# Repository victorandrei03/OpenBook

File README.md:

# OpenBook - 331CC Preda Victor-Andrei

## 📋 Descriere Proiect
Acest proiect reprezintă o placă electronică (e-board) customizată, proiectată în Autodesk Fusion 360. Include:
- Schematică completă
- Design PCB
- Design 3D al carcasei
- Listă completă de componente (BOM)

## 🗂️ Diagrama bloc

## 🛠️ Componente Cheie
| Componentă | Model | Descriere |
|------------|-------|-----------|
| **Microcontroler** | ESP32-C6-WROOM-1-N8 | MCU principal cu WiFi/Bluetooth LE |
| **Ceas RTC** | DS3231SN# | Ceas în timp real cu compensare de temperatură |
| **Senzori** | BME680 | Senzor ambiental (temperatură, umiditate, presiune, VOC) |
| **Management Power** | BD5229G-TR + MCP73831 | Sistem complet de încărcare baterii |

## 📊 Bill of Materials (BOM)

### 🔌 Conectori & Interfețe
| Part Name | Device | Link |
|-----------|--------|------|
| J1 | FH34SRJ-24S-0.5SH_99_ | [Datasheet](https://componentsearchengine.com/part-view/XC6220A331MR-G/Torex) |
| J2 | USB4110-GF-A | [Mouser](https://componentsearchengine.com/part-view/USB4110-GF-A/GCT) |
| J3 | QWIIC_CONNECTORJS-1MM | [SparkFun](https://www.sparkfun.com/products/14417) |

### 💾 Memorie & Storage
| Part Name | Device | Link |
|-----------|--------|------|
| U1 | W25Q512JVEIQ | [Winbond](https://www.snapeda.com/parts/W25Q512JVEIQ/Winbond+Electronics/view-part/) |

### ⚡ Power Management
| Part Name | Device | Link |
|-----------|--------|------|
| IC1 | BD5229G-TR | [ROHM](https://componentsearchengine.com/part-view/BD5229G-TR/ROHM) |
| U4 | MAX17048G+T10 | [Analog Devices](https://www.snapeda.com/parts/MAX17048G+T10/Analog+Devices/view-part/) |

### 🎚️ Componente Pasive
| Categorie | Qty | Device | Link |
|-----------|-----|--------|------|
| **Rezistoare** | 25+ | RR0402 100K | [YAGEO](https://componentsearchengine.com/part-view/R0402%201%25%20100%20K/YAGEO) |
| **Condensatoare** | 20+ | CC0402 1µF | [YAGEO](https://componentsearchengine.com/part-view/CC0402MRX5R5BB106/YAGEO) |
| **Inductoare** | 1 | 744043680 | [Würth](https://eu.mouser.com/ProductDetail/Wurth-Elektronik/744043680) |

### 🛑 Protecții & Diodes
| Part Name | Device | Link |
|-----------|--------|------|
| D1 | USBLC6-2SC6Y | [STMicro](https://www.snapeda.com/parts/USBLC6-2SC6Y/STMicroelectronics/view-part/) |
| D3-D5 | MBR0530 | [Mouser](https://eu.mouser.com/ProductDetail/KYOCERA-AVX/SD0805S020S1R0) |

## 🛠️ Descriere Hardware Detaliată

### 1. Microcontroller - ESP32-C6-WROOM-1-N8
**Specificații Avansate:**
- **Arhitectură:** RISC-V single-core cu 160MHz (configurabil dinamic)
- **Memorie:**
  - 320KB SRAM intern (pentru date)
  - 512KB ROM (pentru bootloader)
  - 8MB Flash SPI (W25Q512JVEIQ) - stochează firmware și date utilizator
- **Conectivitate:**
  - **WiFi 6** (802.11ax) cu throughput de până la 300Mbps
  - **Bluetooth 5 LE** cu support Mesh
  - **Zigbee 3.0** pentru IoT industrial
- **Periferice Integrate:**
  - 4× controller SPI (inclusiv Quad-SPI)
  - 2× I²C (software configurable)
  - 2× UART (cu flow control hardware)
  - 1× USB 2.0 OTG Full-Speed

**Management Energie:**
- **Moduri de operare:**
  - Active Mode: 80mA @ 160MHz
  - Light Sleep: 1.5mA (perif. RAM păstrate)
  - Deep Sleep: 20µA (doar RTC activ)
- **Feature-uri speciale:**
  - Wake-up din Deep Sleep prin:
    - GPIO
    - Timer RTC
    - UART
    - Senzor BME680 (via interrupt)
   
---

### 2. Sistem de Alimentare

**Componente Cheie:**
1. **MCP73831**
   - Curent de încărcare programabil: 100-500mA
   - Protecții integrate: Over-voltage, Reverse discharge
   - LED indicator de stare (conectat la GPIO18)

2. **BD5229G-TR**
   - Eficiență 92% @ 500mA load
   - Ripple voltage < 50mV
   - Shutdown current < 1µA

3. **MAX17048G+T10**
   - Precizie măsurare: ±1% SOC
   - Alertă baterie critică (conectat la GPIO15)
   - Consum propriu: 7µA în mod normal

---

### 3. Senzori & Periferice

#### 3.1 Senzor Environmental BME680
**Interfață:** I²C @ 400kHz (adresă 0x76)  
**Caracteristici unice:**
- **Algoritm BSEC** pentru calcul IAQ (Indice Calitate Aer)
- **Compensare automată** a variațiilor de temperatură
- **Calibrare în fabrică** pentru precizie ridicată

**Conexiuni:**
| Pin BME680 | Pin ESP32 | Notă |
|------------|-----------|------|
| VDD        | 3.3V      | Alimentare filtrată |
| GND        | GND       | - |
| SDA        | GPIO1     | Cu pull-up 4.7kΩ |
| SCL        | GPIO2     | Cu pull-up 4.7kΩ |

#### 3.2 Real-Time Clock DS3231SN#
**Precizie:** ±2ppm (echiv. ~1min/an)  
**Backup:** Supercondensator CPH3225A (10F @ 3.3V)  
**Funcționalități:**
- Alarmă programabilă
- Output square wave (1Hz-32kHz)
- Temperatură internă compensată

---

### 4. Interfețe Externe

#### 4.1 Port USB-C
**Implementare:**
- **Controler:** USB PHY integrat în ESP32-C6
- **Protecții:**
  - ESD: USBLC6-2SC6Y (8kV IEC61000-4-2)
  - Current limit: Polyfuse 500mA

**Funcționalități:**
1. Încărcare baterie
2. Serial Console (CDC-ACM)
3. Update firmware (DFU mode)

#### 4.2 Conector Qwiic
**Aplicații:**
- Conectare senzori adiționali
- Debug I²C bus
- Extensii custom

---

## 🔌 Mapare Pini ESP32-C6

| Pin ESP32-C6 | Componentă / Semnal | Motivul Alegerii |
|--------------|----------------------|------------------|
| **GPIO1 (SDA)** | Magistrală I²C (BME680, MAX17048, DS3231) | Permite comunicarea simultană cu multiple dispozitive prin protocol standard |
| **GPIO2 (SCL)** | Semnal de sincronizare I²C | Asigură temporizarea corectă a transferurilor pe magistrala shared I²C |
| **GPIO5** | SPI MISO (E-Paper) | Facilitatează recepția datelor de stare de la display |
| **GPIO6** | SPI MOSI (E-Paper) | Canal dedicat pentru transmiterea imaginilor către ecran |
| **GPIO7** | SPI CLK (E-Paper) | Generează semnalul de ceas pentru sincronizarea datelor SPI |
| **GPIO8** | SPI CS (E-Paper) | Selectează exclusiv display-ul în configurații multi-slave |
| **GPIO9** | E-Paper DC | Determină dacă transferul conține date sau comenzi |
| **GPIO10** | E-Paper RST | Permite resetarea hardware a display-ului în caz de eroare |
| **GPIO11** | E-Paper BUSY | Monitorizează starea de ocupat pentru sincronizare fără polling |
| **GPIO12** | BUTTON_BOOT | Configurat special pentru intrare în modul de programare |
| **GPIO13** | BUTTON_RESET | Asigură resetarea controlată a sistemului |
| **GPIO14** | BUTTON_USER | Permite interacțiunea utilizatorului cu meniul principal |
| **GPIO15** | MAX17048 ALERT | Semnalează stări critice ale bateriei prin interrupt |
| **GPIO16** | USB D+ | Implementare directă a fizicului USB conform specificației |
| **GPIO17** | USB D- | Pereche diferențială obligatorie pentru comunicarea USB |
| **GPIO18** | STATUS_LED | Oferă feedback vizual despre starea sistemului |
| **GPIO19** | SD Card CS | Selectează cardul SD în arhitectura SPI shared |
| **GPIO20** | SD Card MISO | Primește date de la memoria externă |
| **GPIO21** | SD Card MOSI | Transmite comenzi și date către cardul SD |
| **GPIO4** | SD Card CLK | Asigură sincronizarea transferurilor SPI către/storage |

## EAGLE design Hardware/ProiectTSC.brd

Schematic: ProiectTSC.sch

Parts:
BOOT_BUTTON1: BUTTON_CUSYOMV1; MYBUTTON
C1, C2, C4_USB, C6, C8, C9, C10: 100nF; EAGLE-LTSPICE_C0402
C1_BAT, C1_BAT1, C1_BAT2: 4.7uF; ESP32_WROVER_EAGLE-LTSPICE_C0402
C2_BAT, C5_USB: 4.7uF; EAGLE-LTSPICE_C0402
C3: 100uF; RCL_CT3528
C4: 4.7uF/25V; ESP32_WROVER_EAGLE-LTSPICE_C0402
C5: 1uF; EAGLE-LTSPICE_C0402
C7: 10uF; ESP32_WROVER_EAGLE-LTSPICE_C0402
C10_SUPERCAP: CPH3225A; CAPCP3225X100N
CHANGE_BUTTON: BUTTON_CUSYOMV1; MYBUTTON
CHG_LED: ADAFRUIT_LEDCHIP-LED0603; ADAFRUIT_CHIP-LED0603
C_DELAY: 100nF; EAGLE-LTSPICE_C0402
D1: USBLC6-2SC6Y; SOT95P280X145-6N
D2, D7: ESP32_WROVER_AVX---SD0805S020S1R0_AVX_SD0805S020S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; ESP32_WROVER_AVX---SD0805S020S1R0_AVX_SD0805S020S1R0_0
D3, D4, D5: MBR0530; SOD3716X135N
D6, D8, D9, D10, D11, D12: PGB1010603MR; DIOC1608X36N
EPD_C1, EPD_C2, EPD_C6, EPD_C7, EPD_C8, EPD_C9, EPD_C10, EPD_C11, EPD_C12: 1uF/50V; EAGLE-LTSPICE_C0402
EPD_C5: 0.1uF/50V; EAGLE-LTSPICE_C0402
IC1: BD5229G-TR; SOT95P280X125-5N
IC4: XC6220A331MR-G; SOT95P280X120-5N
J1: FH34SRJ-24S-0.5SH_99_; FH34SRJ24S05SH99
J2: SAMACSYS_PARTS_USB4110-GF-A; SAMACSYS_PARTS_USB4110GFA
J3: QWIIC_RIGHT_ANGLE; JST04_1MM_RA
J4: 112A-TAAR-R03_ATTEND; 112ATAARR03ATTEND
L1: 68uH; IND_4828-WE-TPC_WRE
MCP73831: ESP32_WROVER_SPARKFUN-IC-POWER_MCP73831; ESP32_WROVER_SPARKFUN-IC-POWER_SOT23-5
PFMF.050.1: ESP32C6_VARISTORCN1812; ESP32C6_VARISTOR_CT/CN1812
Q1, Q2: 20V/4.2A/52mΩ/1.4W; ESP32_WROVER_SPARKFUN-DISCRETESEMI_SOT23-3
Q3: SI1308EDL-T1-GE3; SOT65P210X110-3N
R1: 10k; ESP32_WROVER_EAGLE-LTSPICE_R0402
R1_BAT: 200; ESP32_WROVER_EAGLE-LTSPICE_R0402
R1_PINH, R1_PINH1, R1_PWRUSB, R2_PINH, R2_PINH1, R4, R5, R6, R7, R8, R9, R10: 10K; ESP32_WROVER_EAGLE-LTSPICE_R0402
R2: 2.2; ESP32_WROVER_EAGLE-LTSPICE_R0402
R2-USB, R2-USB1: 5k1; ESP32_WROVER_EAGLE-LTSPICE_R0402
R2_BAT: 2k; ESP32_WROVER_EAGLE-LTSPICE_R0402
R3: 0.47; ESP32_WROVER_EAGLE-LTSPICE_R0402
RESET_BUTTON: BUTTON_CUSYOMV1; MYBUTTON
R_BOOT: 10K; ESP32_WROVER_EAGLE-LTSPICE_R0402
R_CAPACITOR: 15; ESP32_WROVER_EAGLE-LTSPICE_R0402
R_CHANGE: 10K; ESP32_WROVER_EAGLE-LTSPICE_R0402
R_CL1: 10K; ESP32_WROVER_EAGLE-LTSPICE_R0402
R_RESET: 10K; ESP32_WROVER_EAGLE-LTSPICE_R0402
SENSOR2: ESP32_WROVER_BME680_BME680; ESP32_WROVER_BME680_PSON80P300X300X100-8N
SJ1: SJ
TP3, TP6, TP14: TPTP20R; TP20R
TP_3V3: TPTP20R; TP20R
TP_EPD_3V3, TP_EPD_3V3_C: TPTP20R; TP20R
TP_EPD_BUSY: TPTP20R; TP20R
TP_EPD_CS: TPTP20R; TP20R
TP_EPD_DC: TPTP20R; TP20R
TP_EPD_RST: TPTP20R; TP20R
TP_GND, TP_GND1: TPTP20R; TP20R
TP_INT_RT: TPTP20R; TP20R
TP_MOSI: TPTP20R; TP20R
TP_RX: TPTP20R; TP20R
TP_SCK: TPTP20R; TP20R
TP_TX: TPTP20R; TP20R
U1: W25Q512JVEIQ; SON127P600X800X80-9N
U2: ESP32-C6-WROOM-1-N8; XCVR_ESP32-C6-WROOM-1-N8
U3: DS3231SN#; SOIC127P1032X265-16N
U4: MAX17048G+T10; SON50P200X200X80-9N

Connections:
3V3: C1_BAT2.1, C3.+, C9.1, D7.2 (ANODE), IC1.2 (VDD), IC4.5 (VOUT), J3.2, J4.P4 (VDD), Q2.3 (D), R1.2, R1_PINH1.2, R2_PINH1.2, R5.2, R6.2, R7.2, R8.2, R9.2, R10.2, R_BOOT.2, R_CHANGE.2, R_CL1.2, R_RESET.2, TP_3V3.TP, U1.3 (!WP!(IO2)), U1.7 (!HOLD!/!RESET!(IO3)), U1.8 (VCC), U2.2 (3V3), U3.2 (VCC)
32KHZ: R2_PINH1.1, U2.9 (IO1), U3.1 (32KHZ)
DN: D1.4 (I/O2_2), J2.A7, J2.B7
DP: D1.6 (I/O1_2), J2.A6, J2.B6
EPD_3V3: C7.1, EPD_C5.1, J1.15, J1.16, L1.2, Q2.2 (S), TP_EPD_3V3.TP
EPD_3V3_C: Q2.1 (G), R_CL1.1, TP_EPD_3V3_C.TP, U2.18 (IO20)
EPD_BUSY: J1.9, TP_EPD_BUSY.TP, U2.26 (IO3)
EPD_CS: D6.2, J1.12, R9.1, TP_EPD_CS.TP, U2.11 (IO10)
EPD_DC: J1.11, TP_EPD_DC.TP, U2.5 (IO5)
EPD_RST: J1.10, TP_EPD_RST.TP, U2.21 (IO23)
FLASH_CS: D9.2, R5.1, U1.1 (!CS), U2.12 (IO11)
GDR: J1.2, Q3.1 (G), R4.2
GND: BOOT_BUTTON1.1, BOOT_BUTTON1.2, C1.2, C1_BAT.2, C1_BAT1.2, C1_BAT2.2, C2.2, C2_BAT.2, C3.-, C4_USB.2, C5.2, C5_USB.2, C6.2, C7.2, C8.2, C9.2, C10.2, C10_SUPERCAP.2, CHANGE_BUTTON.1, CHANGE_BUTTON.2, C_DELAY.2, D1.2 (GND), D3.1 (K), D6.1, D8.1, D9.1, D10.1, D11.1, D12.1, EPD_C1.2, EPD_C2.2, EPD_C5.2, EPD_C6.2, EPD_C7.2, EPD_C8.2, EPD_C9.2, EPD_C10.2, EPD_C11.2, EPD_C12.2, IC1.3 (GND), IC4.2 (VSS), J1.8, J1.17, J1.MP1, J1.MP2, J2.A1, J2.A12, J2.B1, J2.B12, J2.MP1, J2.MP2, J2.MP3, J2.MP4, J3.1, J4.G1 (GND_1), J4.G2 (GND_2), J4.G3 (GND_3), J4.G4 (GND_4), J4.P6 (VSS), MCP73831.2 (VSS), R1_PWRUSB.1, R2.1, R2-USB.2, R2-USB1.1, R2_BAT.1, R4.1, RESET_BUTTON.1, RESET_BUTTON.2, SENSOR2.1 (GND), SENSOR2.5 (SDO), SENSOR2.7 (GND), SJ1.1, TP_GND.TP, TP_GND1.TP, U1.4 (GND), U1.9 (EXP), U2.1 (GND), U2.28 (GND), U2.29_1 (GND), U2.29_2 (GND), U2.29_3 (GND), U2.29_4 (GND), U2.29_5 (GND), U2.29_6 (GND), U2.29_7 (GND), U2.29_8 (GND), U2.29_9 (GND), U3.13 (GND), U4.1 (CTG), U4.4 (GND), U4.6 (QSTRT), U4.9 (EP)
GPIO8: R1.1, U2.10 (IO8)
I2C_PW: R1_PINH.2, R2_PINH.2, SENSOR2.2 (CSB), SENSOR2.6 (VDDIO), SENSOR2.8 (VDD), U2.17 (IO19)
INT_RTC: R1_PINH1.1, TP_INT_RT.TP, U2.8 (IO0), U3.3 (SQW/!INT)
IO/BOOT: BOOT_BUTTON1.3, BOOT_BUTTON1.4, C6.1, R_BOOT.1, U2.15 (IO9)
IO/CHANGE: C10.1, CHANGE_BUTTON.3, CHANGE_BUTTON.4, R_CHANGE.1, U2.23 (IO15)
MISO: D12.2, J4.P7 (DAT0), R8.1, TP6.TP, U1.2 (DO(IO1)), U2.27 (IO2)
MOSI: D11.2, J1.14, J4.P3 (CMD), R7.1, TP_MOSI.TP, U1.5 (DI(IO0)), U2.7 (IO7)
unnamed: J2.A5, R2-USB1.2
unnamed: C1_BAT1.1, D2.1 (CATHODE), IC4.1 (VIN), IC4.3 (CE), Q1.2 (S)
unnamed: J2.B5, R2-USB.1
unnamed: CHG_LED.C, R1_BAT.1
unnamed: C4.1, D3.2 (A), D4.1 (K)
unnamed: MCP73831.1 (STAT), R1_BAT.2
unnamed: EPD_C12.1, J1.24
unnamed: MCP73831.5 (PROG), R2_BAT.2
unnamed: EPD_C1.1, J1.4
unnamed: EPD_C2.1, J1.5
unnamed: EPD_C10.1, J1.22
unnamed: EPD_C8.1, J1.20
unnamed: EPD_C7.1, J1.19
unnamed: EPD_C6.1, J1.18
unnamed: C1.1, C2.1
unnamed: C_DELAY.1, IC1.5 (CT)
unnamed: D7.1 (CATHODE), R_CAPACITOR.1
PREVGH: D5.1 (K), EPD_C9.1, J1.21
PREVGL: D4.2 (A), EPD_C11.1, J1.23
RESE: J1.3, Q3.2 (S), R3.2
RESE': R2.2, R3.1, SJ1.2
RESET: C5.1, IC1.1 (VOUT), RESET_BUTTON.3, RESET_BUTTON.4, R_RESET.1, U2.3 (EN)
RTC_RST: U2.16 (IO18), U3.4 (!RST)
RX: TP_RX.TP, U2.24 (RXD0/GPIO17)
SCK: D10.2, J1.13, J4.P5 (CLK), R6.1, TP_SCK.TP, U1.6 (CLK), U2.6 (IO6)
SCL: J3.4, R2_PINH.1, SENSOR2.4 (SCK), U2.20 (IO22), U3.16 (SCL), U4.7 (SCL)
SDA: J3.3, R1_PINH.1, SENSOR2.3 (SDI), U2.19 (IO21), U3.15 (SDA), U4.8 (SDA)
SRC: C4.2, D5.2 (A), L1.1, Q3.3 (D)
SS_SD: D8.2, J4.P2 (CD/DAT3), R10.1, U2.4 (IO4)
TX: TP_TX.TP, U2.25 (TXD0/GPIO16)
USB_D+: D1.1 (I/O1_1), U2.14 (IO13)
USB_D-: D1.3 (I/O2_1), U2.13 (IO12)
VBAT: C2_BAT.1, MCP73831.3 (VBAT), Q1.3 (D), TP3.TP, U4.2 (CELL), U4.3 (VDD)
VBUS: C1_BAT.1, C4_USB.1, C5_USB.1, CHG_LED.A, D1.5 (VBUS), D2.2 (ANODE), MCP73831.4 (VIN), PFMF.050.1.2, Q1.1 (G), R1_PWRUSB.2, TP14.TP
VRTC: C8.1, C10_SUPERCAP.1, R_CAPACITOR.2, U3.14 (VBAT)
VUSB: J2.A4, J2.A9, J2.B4, J2.B9, PFMF.050.1.1

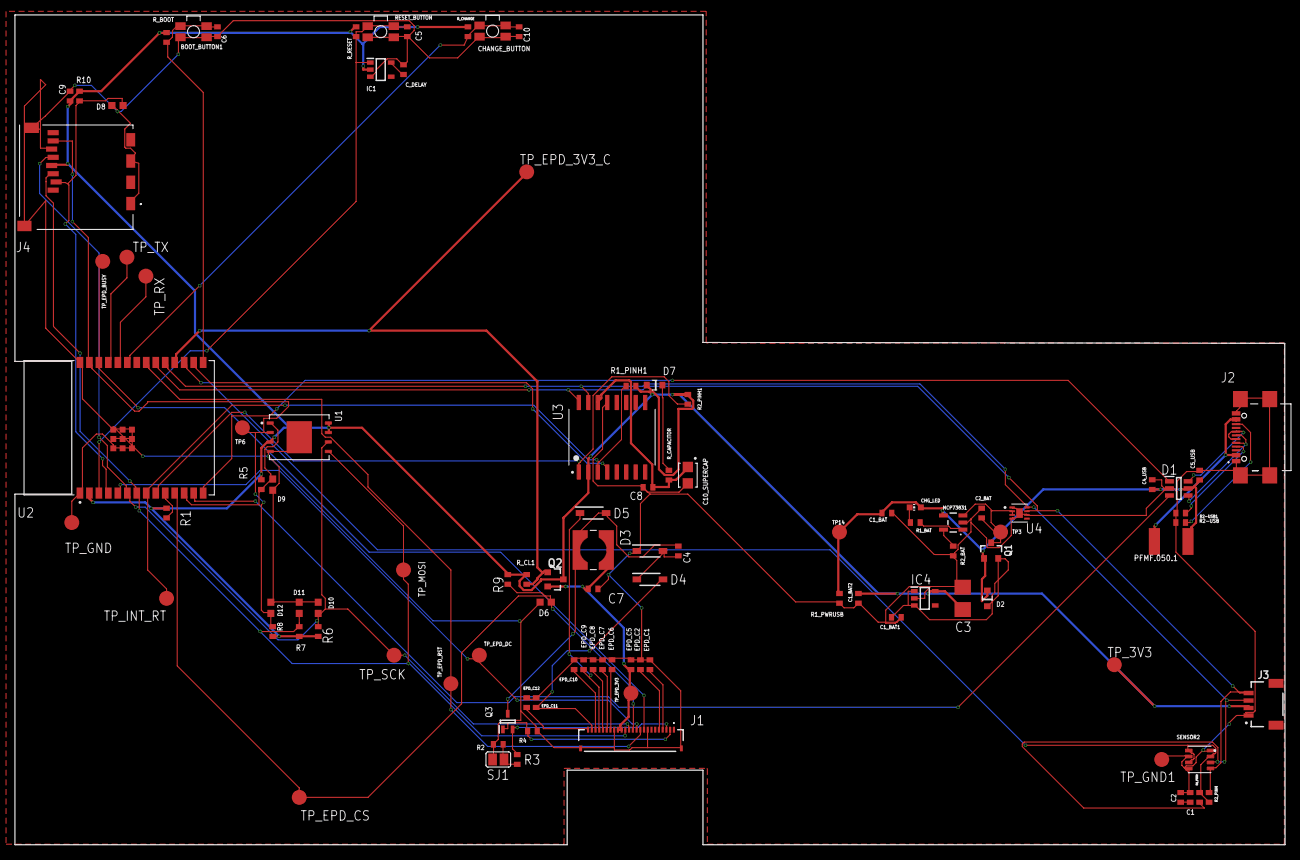
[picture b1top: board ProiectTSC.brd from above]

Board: 2 copper layers, 170.2 x 111.2 mm, 103 parts (0 on the bottom side), 56 nets.

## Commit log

2025-04-06 Create LICENSE
2025-04-06 Upload project
2025-04-11 Update Hardware
2025-04-11 Update Mechanical

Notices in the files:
parts and their libraries:
COPYRIGHT: Copyright (C) 2024 Ultra Librarian. All rights reserved.
